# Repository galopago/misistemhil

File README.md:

# MISISTEMHIL

## INTERFACE FOR AUTOMATED TESTS (HARDWARE-IN-THE-LOOP). SOLDERLESS, MODULAR AND OPEN SOURCE

Electronic hardware prototyping system. Solderless, robust and open source. Solves the typical problem of the circuit that works on a breadboard but stops working on a real-world setup. Easy to replicate and compatible with virtually every electronic module.

Misistemhil is an open source project by [Galopago](https://galopago.github.io/)

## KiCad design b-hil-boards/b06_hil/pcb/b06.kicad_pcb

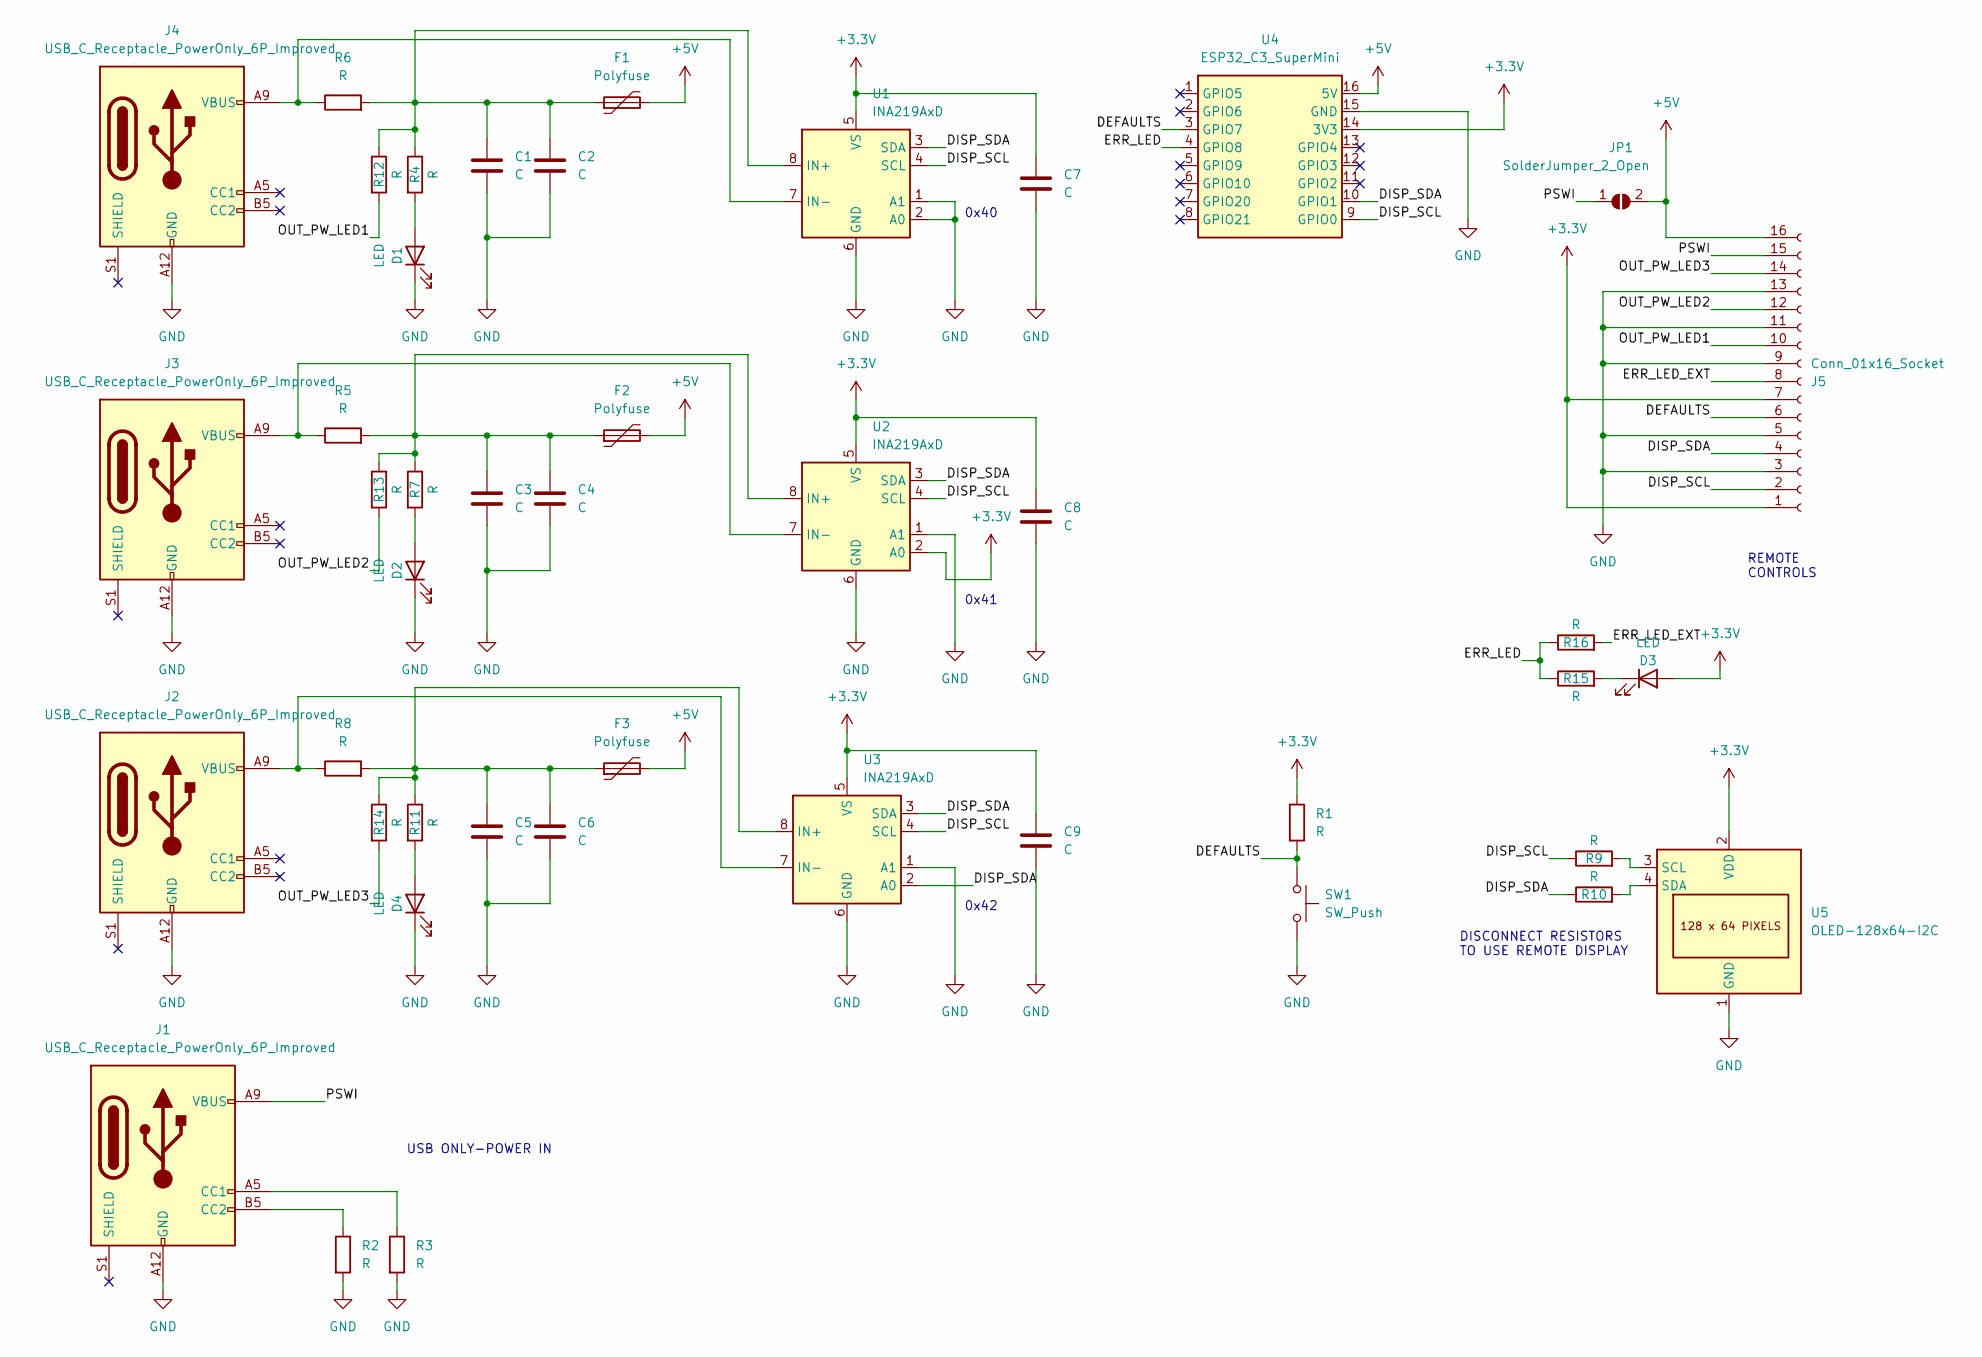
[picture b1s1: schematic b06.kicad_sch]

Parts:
C1, C3, C5: C; CP_Elec_8x10.5
C2, C4, C6, C7, C8, C9: C; C_0805_2012Metric_Pad1.18x1.45mm_HandSolder
D1, D2, D3, D4: LED; LED_0805_2012Metric_Pad1.15x1.40mm_HandSolder
F1, F2, F3: Polyfuse; Fuse_1206_3216Metric_Pad1.42x1.75mm_HandSolder
J1, J2, J3, J4: USB_C_Receptacle_PowerOnly_6P_Improved; USB_C_Receptacle_HRO_TYPE-C-31-M-12
J5: Conn_01x16_Socket; TerminalBlock_DoubleLevel_2x08_P3.50mm_Horizontal
JP1: SolderJumper_2_Open; SolderJumper-2_P1.3mm_Open_RoundedPad1.0x1.5mm
R1, R2, R3, R4, R7, R9, R10, R11, R12, R13, R14, R15, R16: R; R_0805_2012Metric_Pad1.20x1.40mm_HandSolder
R5, R6, R8: R; R_2512_6332Metric_Pad1.40x3.35mm_HandSolder
SW1: SW_Push; SW_Push_1P1T_NO_6x6mm_H9.5mm
U1, U2, U3: INA219AxD; SOIC-8_3.9x4.9mm_P1.27mm
U4: ESP32_C3_SuperMini; ESP32 C3 SuperMini
U5: OLED-128x64-I2C

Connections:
+3.3V: C7.1, C8.1, C9.1, D3.2 (A), J5.1, J5.7, R1.1, U1.5 (VS), U2.2 (A0), U2.5 (VS), U3.5 (VS), U4.14 (3V3), U5.2 (VDD)
+5V: F1.2, F2.2, F3.2, J5.16, JP1.2 (B), U4.16 (5V)
/DEFAULTS: J5.6, R1.2, SW1.1, U4.3 (GPIO7)
/DISP_SCL: J5.2, R9.1, U1.4 (SCL), U2.4 (SCL), U3.4 (SCL), U4.9 (GPIO0)
/DISP_SDA: J5.4, R10.1, U1.3 (SDA), U2.3 (SDA), U3.2 (A0), U3.3 (SDA), U4.10 (GPIO1)
/ERR_LED: R15.1, R16.1, U4.4 (GPIO8)
/ERR_LED_EXT: J5.8, R16.2
/OUT_PW_LED1: J5.10, R12.2
/OUT_PW_LED2: J5.12, R13.2
/OUT_PW_LED3: J5.14, R14.2
/PSWI: J1.A4 (VBUS), J1.A9 (VBUS), J1.B4 (VBUS), J1.B9 (VBUS), J5.15, JP1.1 (A)
GND: C1.2, C2.2, C3.2, C4.2, C5.2, C6.2, C7.2, C8.2, C9.2, D1.1 (K), D2.1 (K), D4.1 (K), J1.A1 (GND), J1.A12 (GND), J1.B1 (GND), J1.B12 (GND), J2.A1 (GND), J2.A12 (GND), J2.B1 (GND), J2.B12 (GND), J3.A1 (GND), J3.A12 (GND), J3.B1 (GND), J3.B12 (GND), J4.A1 (GND), J4.A12 (GND), J4.B1 (GND), J4.B12 (GND), J5.3, J5.5, J5.9, J5.11, J5.13, R2.2, R3.2, SW1.2, U1.1 (A1), U1.2 (A0), U1.6 (GND), U2.1 (A1), U2.6 (GND), U3.1 (A1), U3.6 (GND), U4.15 (GND), U5.1 (GND)
unnamed: D1.2 (A), R4.2
unnamed: D2.2 (A), R7.2
unnamed: D3.1 (K), R15.2
unnamed: D4.2 (A), R11.2
unnamed: J1.A5 (CC1), R3.1
unnamed: J1.B5 (CC2), R2.1
unnamed: C1.1, C2.1, F1.1, R4.1, R6.2, R12.1, U1.8 (IN+)
unnamed: J4.A4 (VBUS), J4.A9 (VBUS), J4.B4 (VBUS), J4.B9 (VBUS), R6.1, U1.7 (IN-)
unnamed: C3.1, C4.1, F2.1, R5.2, R7.1, R13.1, U2.8 (IN+)
unnamed: J3.A4 (VBUS), J3.A9 (VBUS), J3.B4 (VBUS), J3.B9 (VBUS), R5.1, U2.7 (IN-)
unnamed: C5.1, C6.1, F3.1, R8.2, R11.1, R14.1, U3.8 (IN+)
unnamed: J2.A4 (VBUS), J2.A9 (VBUS), J2.B4 (VBUS), J2.B9 (VBUS), R8.1, U3.7 (IN-)
unnamed: R9.2, U5.3 (SCL)
unnamed: R10.2, U5.4 (SDA)

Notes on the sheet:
0x41
0x42
REMOTE CONTROLS
0x40
DISCONNECT RESISTORS TO USE REMOTE DISPLAY
USB ONLY-POWER IN

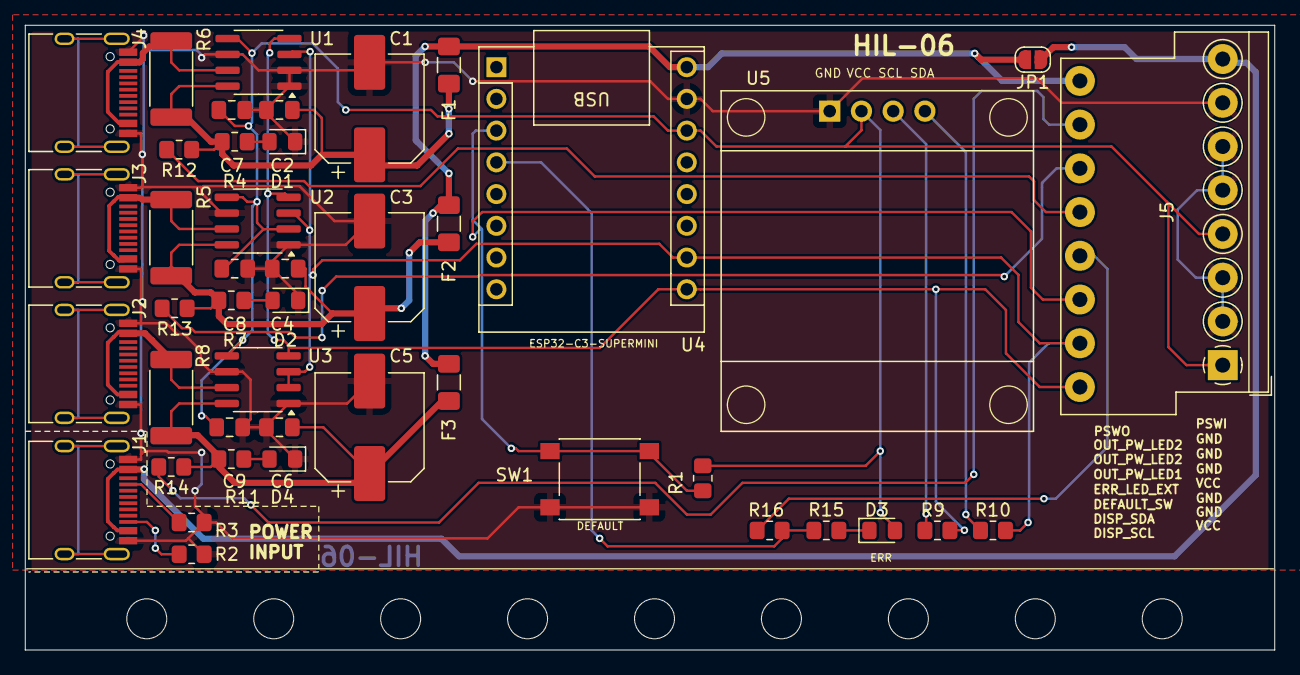
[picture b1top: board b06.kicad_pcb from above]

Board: 2 copper layers, 100.0 x 50.0 mm, 53 parts (0 on the bottom side), 26 nets.

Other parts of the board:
MH01, MH02, MH03, MH04, MH05, MH06, MH07, MH08, MH09: MountingHole_3.2mm_M3

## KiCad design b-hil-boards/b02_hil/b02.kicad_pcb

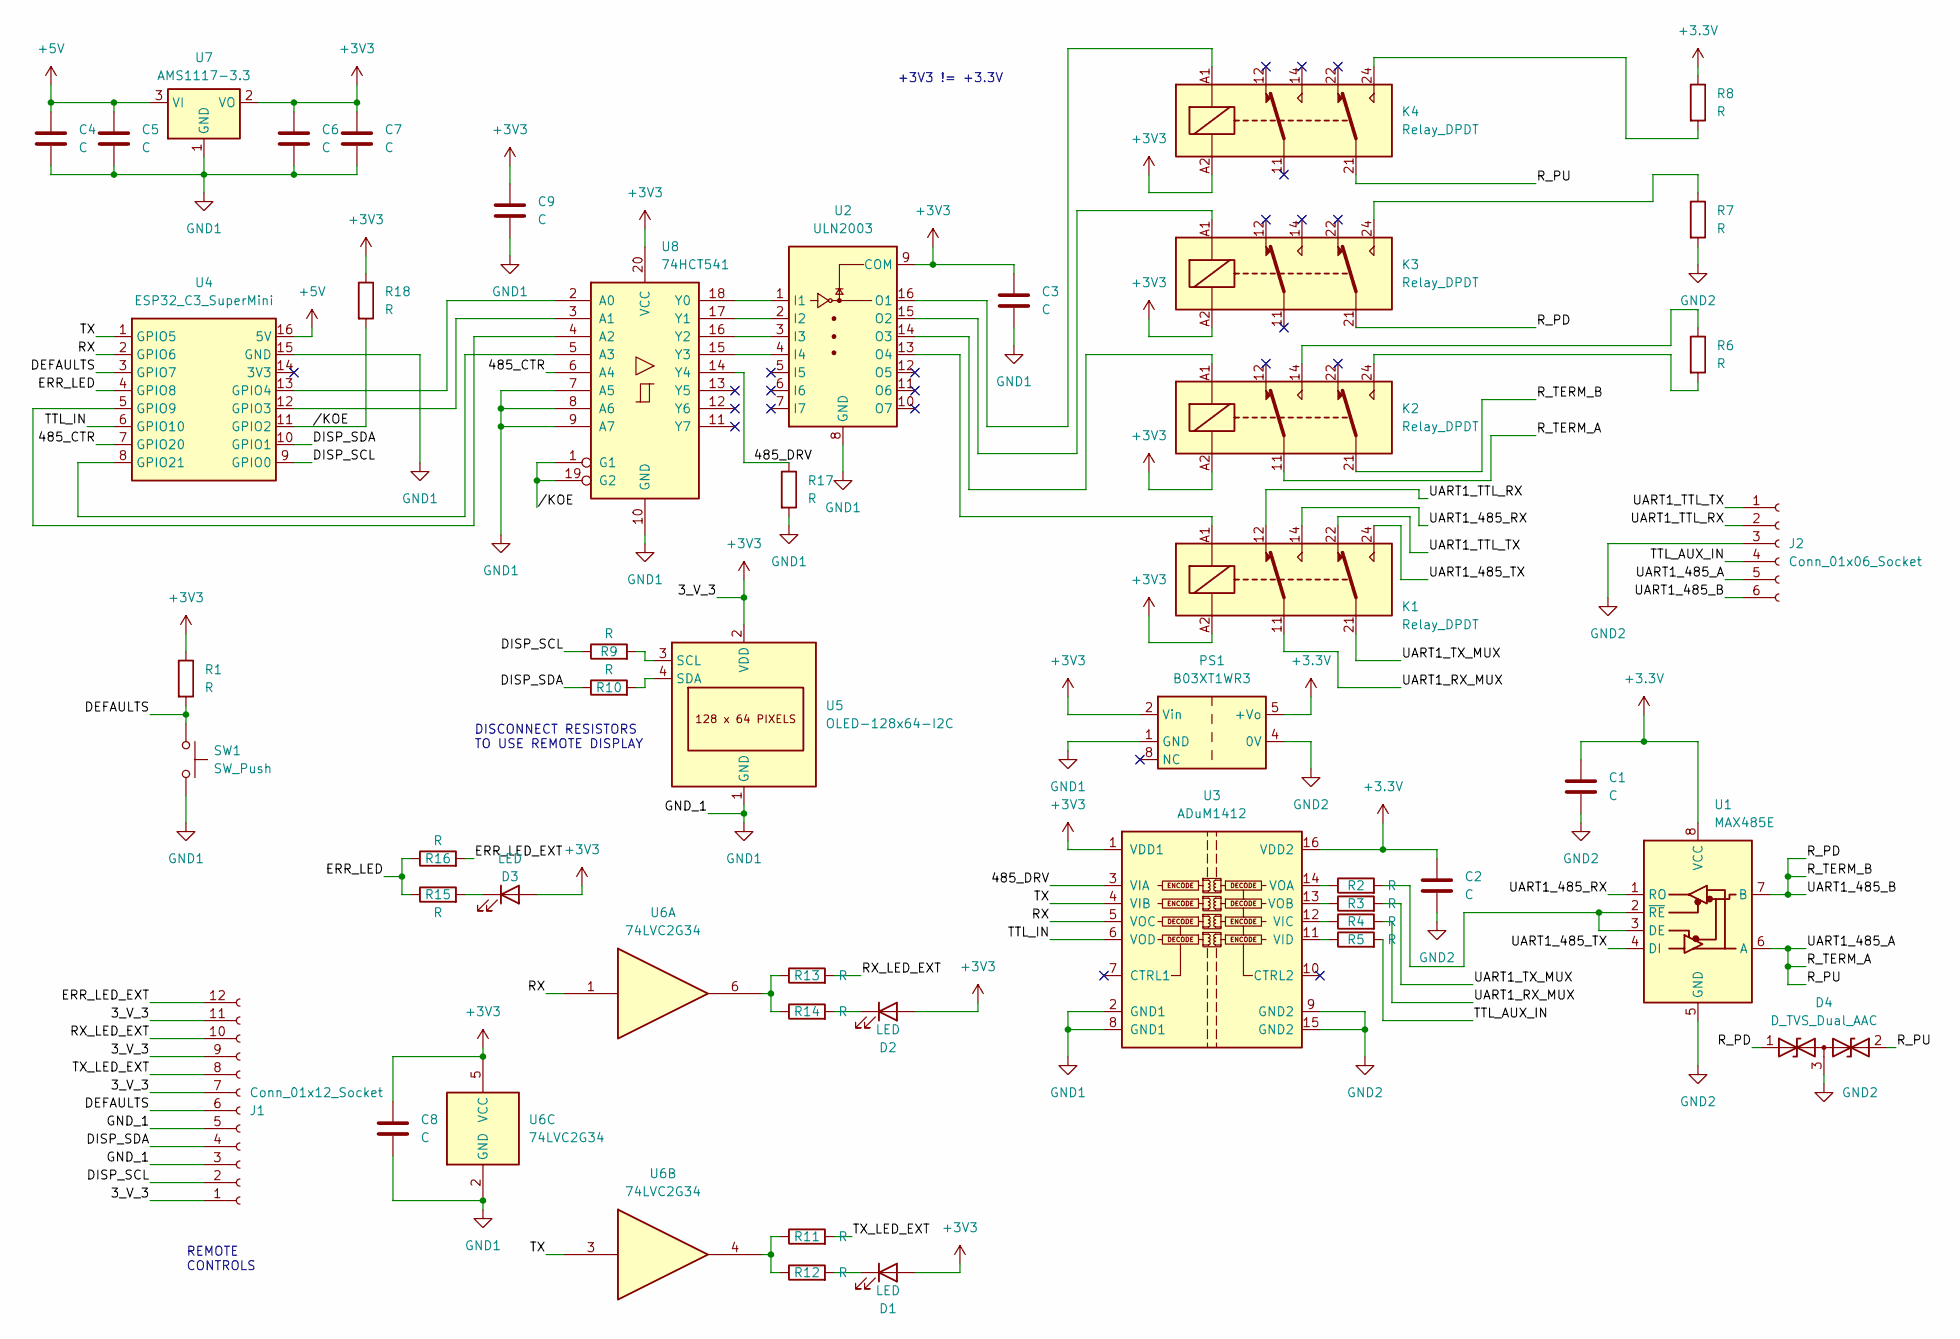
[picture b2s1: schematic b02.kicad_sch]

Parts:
C1, C2, C3, C4, C5, C6, C7, C8, C9: C; C_0805_2012Metric_Pad1.18x1.45mm_HandSolder
D1, D2, D3: LED; LED_0805_2012Metric_Pad1.15x1.40mm_HandSolder
D4: D_TVS_Dual_AAC; SOT-23-3
J1: Conn_01x12_Socket; TerminalBlock_DoubleLevel_2x06_P3.50mm_Horizontal
J2: Conn_01x06_Socket; TerminalBlock_DoubleLevel_2x03_P3.50mm_Horizontal
K1, K2, K3, K4: Relay_DPDT; Relay_DPDT_Omron_G6K-2F-Y
PS1: B03XT1WR3; Converter_DCDC_Mornsun_B03_XT_1WR3_SMD
R1, R2, R3, R4, R5, R6, R7, R8, R9, R10, R11, R12, R13, R14, R15, R16, R17, R18: R; R_0805_2012Metric_Pad1.20x1.40mm_HandSolder
SW1: SW_Push; SW_Push_1P1T_NO_6x6mm_H9.5mm
U1: MAX485E; SOIC-8_3.9x4.9mm_P1.27mm
U2: ULN2003; SOIC-16_3.9x9.9mm_P1.27mm
U3: ADuM1412; SOIC-16W_7.5x10.3mm_P1.27mm
U4: ESP32_C3_SuperMini; ESP32 C3 SuperMini
U5: OLED-128x64-I2C
U6: 74LVC2G34; SOT-23-6_Handsoldering
U7: AMS1117-3.3; SOT-223-3_TabPin2
U8: 74HCT541; TSSOP-20_4.4x6.5mm_P0.65mm

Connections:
+3.3V: C1.1, C2.1, PS1.5 (+Vo), R8.1, U1.8 (VCC), U3.16 (VDD2)
+3V3: C3.1, C6.1, C7.1, C8.1, C9.1, D1.2 (A), D2.2 (A), D3.2 (A), J1.1, J1.7, J1.9, J1.11, K1.A2, K2.A2, K3.A2, K4.A2, PS1.2 (Vin), R1.1, R18.1, U2.9 (COM), U3.1 (VDD1), U5.2 (VDD), U6.5 (VCC), U7.2 (VO), U8.20 (VCC)
+5V: C4.1, C5.1, U4.16 (5V), U7.3 (VI)
/485_CTR: U4.7 (GPIO20), U8.6 (A4)
/485_DRV: R17.1, U3.3 (VIA), U8.14 (Y4)
/DEFAULTS: J1.6, R1.2, SW1.1, U4.3 (GPIO7)
/DISP_SCL: J1.2, R9.1, U4.9 (GPIO0)
/DISP_SDA: J1.4, R10.1, U4.10 (GPIO1)
/ERR_LED: R15.1, R16.1, U4.4 (GPIO8)
/ERR_LED_EXT: J1.12, R16.2
/RX: U3.5 (VOC), U4.2 (GPIO6), U6.1
/RX_LED_EXT: J1.10, R13.2
/R_PD: D4.1 (A1), J2.6, K2.21, K3.21, U1.7 (B)
/R_PU: D4.2 (A2), J2.5, K2.11, K4.21, U1.6 (A)
/TTL_AUX_IN: J2.4, R5.2
/TTL_IN: U3.6 (VOD), U4.6 (GPIO10)
/TX: U3.4 (VIB), U4.1 (GPIO5), U6.3
/TX_LED_EXT: J1.8, R11.2
/UART1_485_RX: K1.14, U1.1 (RO)
/UART1_485_TX: K1.24, U1.4 (DI)
/UART1_RX_MUX: K1.11, R4.2
/UART1_TTL_RX: J2.2, K1.12
/UART1_TTL_TX: J2.1, K1.22
/UART1_TX_MUX: K1.21, R3.2
//KOE: R18.2, U4.11 (GPIO2), U8.1 (G1), U8.19 (G2)
GND1: C3.2, C4.2, C5.2, C6.2, C7.2, C8.2, C9.2, J1.3, J1.5, PS1.1 (GND), R17.2, SW1.2, U2.8 (GND), U3.2 (GND1), U3.8 (GND1), U4.15 (GND), U5.1 (GND), U6.2 (GND), U7.1 (GND), U8.7 (A5), U8.8 (A6), U8.9 (A7), U8.10 (GND)
GND2: C1.2, C2.2, D4.3 (common), J2.3, PS1.4 (0V), R7.2, U1.5 (GND), U3.9 (GND2), U3.15 (GND2)
unnamed: D1.1 (K), R12.2
unnamed: D2.1 (K), R14.2
unnamed: D3.1 (K), R15.2
unnamed: K2.14, R6.1
unnamed: K2.24, R6.2
unnamed: K3.24, R7.1
unnamed: K4.24, R8.2
unnamed: R11.1, R12.1, U6.4
unnamed: R13.1, R14.1, U6.6
unnamed: R2.2, U1.2 (~RE), U1.3 (DE)
unnamed: U2.1 (I1), U8.18 (Y0)
unnamed: U2.2 (I2), U8.17 (Y1)
unnamed: U2.3 (I3), U8.16 (Y2)
unnamed: U2.4 (I4), U8.15 (Y3)
unnamed: K4.A1, U2.16 (O1)
unnamed: K3.A1, U2.15 (O2)
unnamed: K2.A1, U2.14 (O3)
unnamed: K1.A1, U2.13 (O4)
unnamed: R4.1, U3.12 (VIC)
unnamed: R5.1, U3.11 (VID)
unnamed: R2.1, U3.14 (VOA)
unnamed: R3.1, U3.13 (VOB)
unnamed: U4.12 (GPIO3), U8.3 (A1)
unnamed: U4.13 (GPIO4), U8.2 (A0)
unnamed: U4.5 (GPIO9), U8.4 (A2)
unnamed: U4.8 (GPIO21), U8.5 (A3)
unnamed: R9.2, U5.3 (SCL)
unnamed: R10.2, U5.4 (SDA)

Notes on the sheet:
+3V3 != +3.3V
REMOTE CONTROLS
DISCONNECT RESISTORS TO USE REMOTE DISPLAY

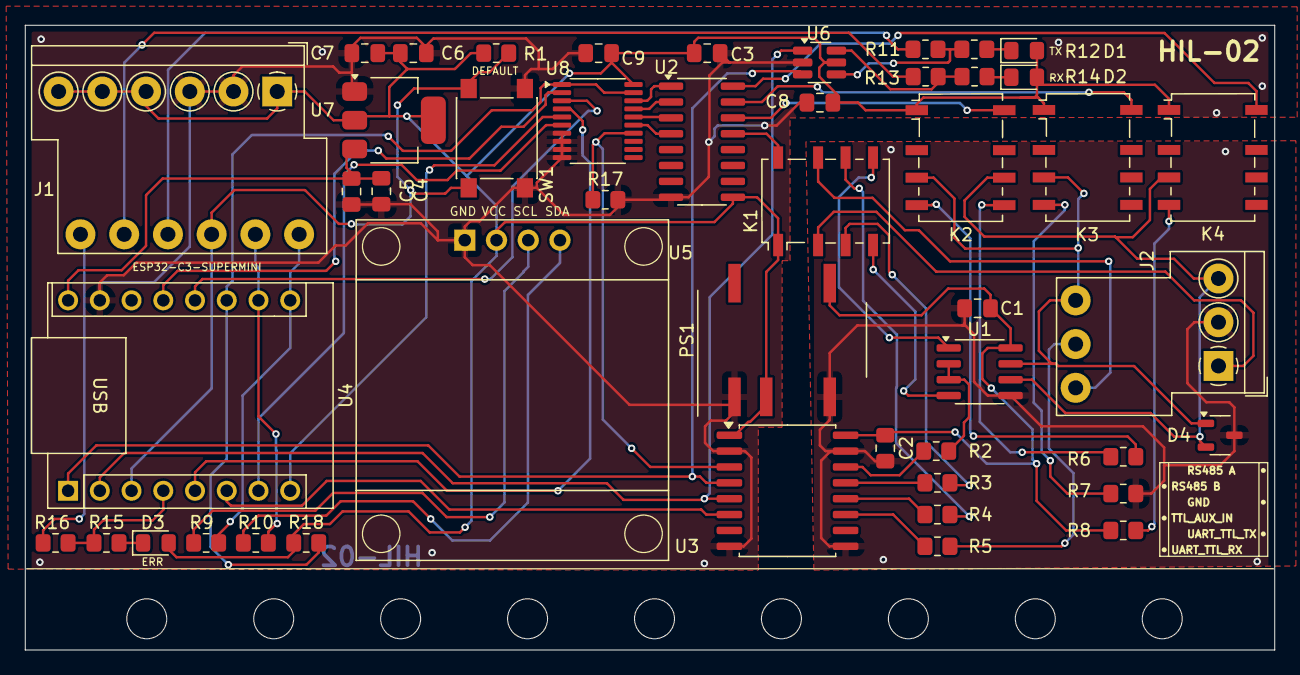
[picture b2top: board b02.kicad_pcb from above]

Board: 2 copper layers, 100.0 x 50.0 mm, 56 parts (0 on the bottom side), 55 nets.

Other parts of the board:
MH01, MH02, MH03, MH04, MH05, MH06, MH07, MH08, MH09: MountingHole_3.2mm_M3

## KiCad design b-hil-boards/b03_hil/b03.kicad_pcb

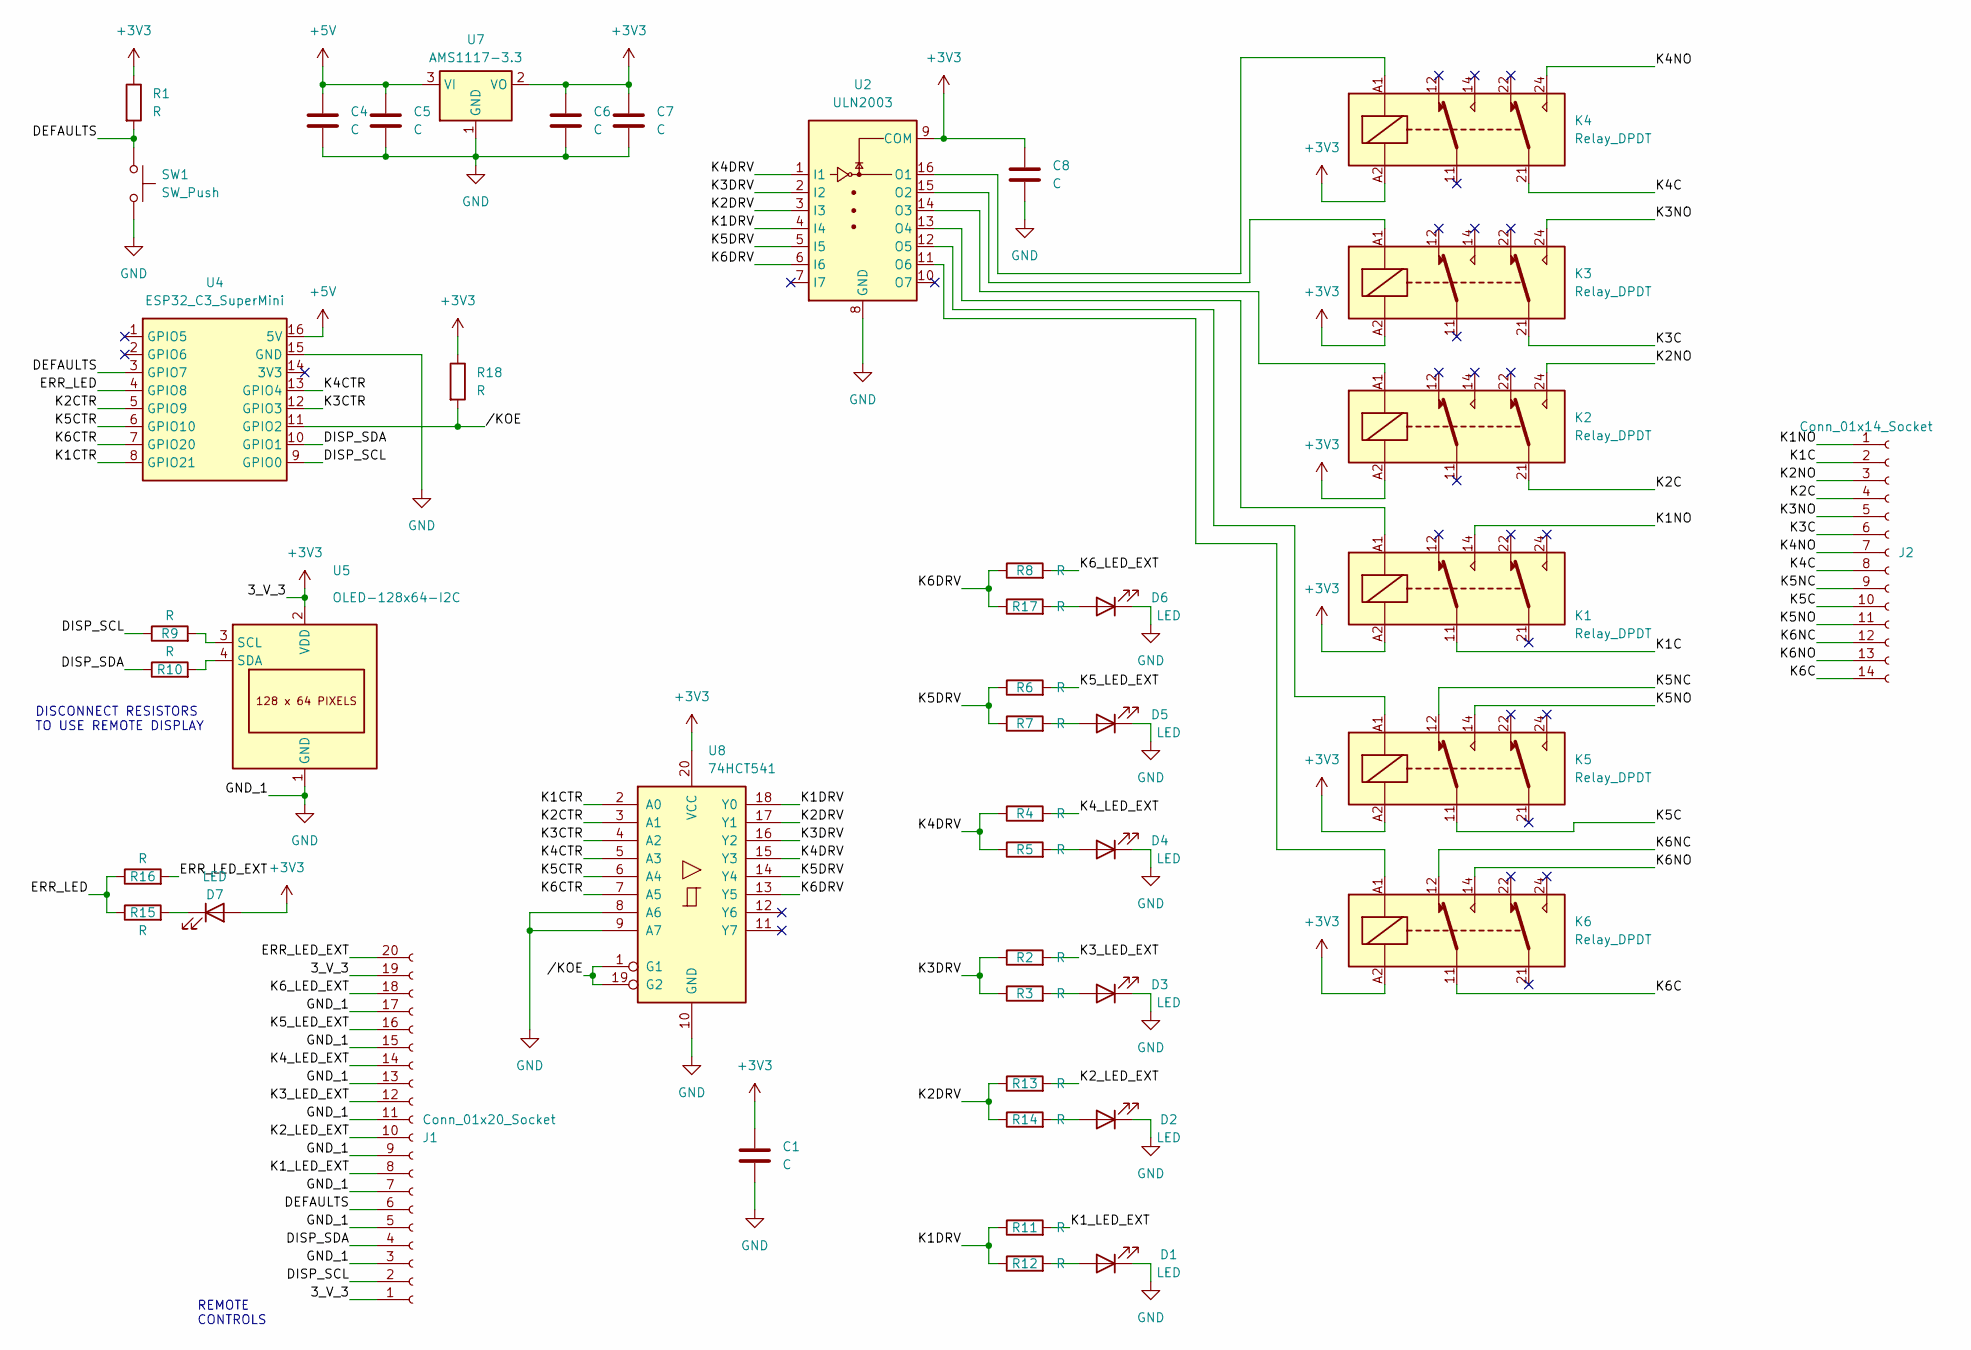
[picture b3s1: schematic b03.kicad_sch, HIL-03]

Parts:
C1, C4, C5, C6, C7, C8: C; C_0805_2012Metric_Pad1.18x1.45mm_HandSolder
D1, D2, D3, D4, D5, D6, D7: LED; LED_0805_2012Metric_Pad1.15x1.40mm_HandSolder
J1: Conn_01x20_Socket; TerminalBlock_DoubleLevel_2x10_P3.50mm_Horizontal
J2: Conn_01x14_Socket; TerminalBlock_DoubleLevel_2x07_P3.50mm_Horizontal
K1, K2, K3, K4, K5, K6: Relay_DPDT; Relay_DPDT_Omron_G6K-2F-Y
R1, R2, R3, R4, R5, R6, R7, R8, R9, R10, R11, R12, R13, R14, R15, R16, R17, R18: R; R_0805_2012Metric_Pad1.20x1.40mm_HandSolder
SW1: SW_Push; SW_Push_1P1T_NO_6x6mm_H9.5mm
U2: ULN2003; SOIC-16_3.9x9.9mm_P1.27mm
U4: ESP32_C3_SuperMini; ESP32 C3 SuperMini
U5: OLED-128x64-I2C
U7: AMS1117-3.3; SOT-223-3_TabPin2
U8: 74HCT541; TSSOP-20_4.4x6.5mm_P0.65mm

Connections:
+3V3: C1.1, C6.1, C7.1, C8.1, D7.2 (A), J1.1, J1.19, K1.A2, K2.A2, K3.A2, K4.A2, K5.A2, K6.A2, R1.1, R18.1, U2.9 (COM), U5.2 (VDD), U7.2 (VO), U8.20 (VCC)
+5V: C4.1, C5.1, U4.16 (5V), U7.3 (VI)
/DEFAULTS: J1.6, R1.2, SW1.1, U4.3 (GPIO7)
/DISP_SCL: J1.2, R9.1, U4.9 (GPIO0)
/DISP_SDA: J1.4, R10.1, U4.10 (GPIO1)
/ERR_LED: R15.1, R16.1, U4.4 (GPIO8)
/ERR_LED_EXT: J1.20, R16.2
/K1C: J2.2, K1.11
/K1CTR: U4.8 (GPIO21), U8.2 (A0)
/K1DRV: R11.1, R12.1, U2.4 (I4), U8.18 (Y0)
/K1NO: J2.1, K1.14
/K1_LED_EXT: J1.8, R11.2
/K2C: J2.4, K2.21
/K2CTR: U4.5 (GPIO9), U8.3 (A1)
/K2DRV: R13.1, R14.1, U2.3 (I3), U8.17 (Y1)
/K2NO: J2.3, K2.24
/K2_LED_EXT: J1.10, R13.2
/K3C: J2.6, K3.21
/K3CTR: U4.12 (GPIO3), U8.4 (A2)
/K3DRV: R2.1, R3.1, U2.2 (I2), U8.16 (Y2)
/K3NO: J2.5, K3.24
/K3_LED_EXT: J1.12, R2.2
/K4C: J2.8, K4.21
/K4CTR: U4.13 (GPIO4), U8.5 (A3)
/K4DRV: R4.1, R5.1, U2.1 (I1), U8.15 (Y3)
/K4NO: J2.7, K4.24
/K4_LED_EXT: J1.14, R4.2
/K5C: J2.10, K5.11
/K5CTR: U4.6 (GPIO10), U8.6 (A4)
/K5DRV: R6.1, R7.1, U2.5 (I5), U8.14 (Y4)
/K5NC: J2.9, K5.12
/K5NO: J2.11, K5.14
/K5_LED_EXT: J1.16, R6.2
/K6C: J2.14, K6.11
/K6CTR: U4.7 (GPIO20), U8.7 (A5)
/K6DRV: R8.1, R17.1, U2.6 (I6), U8.13 (Y5)
/K6NC: J2.12, K6.12
/K6NO: J2.13, K6.14
/K6_LED_EXT: J1.18, R8.2
//KOE: R18.2, U4.11 (GPIO2), U8.1 (G1), U8.19 (G2)
GND: C1.2, C4.2, C5.2, C6.2, C7.2, C8.2, D1.1 (K), D2.1 (K), D3.1 (K), D4.1 (K), D5.1 (K), D6.1 (K), J1.3, J1.5, J1.7, J1.9, J1.11, J1.13, J1.15, J1.17, SW1.2, U2.8 (GND), U4.15 (GND), U5.1 (GND), U7.1 (GND), U8.8 (A6), U8.9 (A7), U8.10 (GND)
unnamed: D1.2 (A), R12.2
unnamed: D2.2 (A), R14.2
unnamed: D3.2 (A), R3.2
unnamed: D4.2 (A), R5.2
unnamed: D5.2 (A), R7.2
unnamed: D6.2 (A), R17.2
unnamed: D7.1 (K), R15.2
unnamed: K4.A1, U2.16 (O1)
unnamed: K3.A1, U2.15 (O2)
unnamed: K2.A1, U2.14 (O3)
unnamed: K1.A1, U2.13 (O4)
unnamed: K5.A1, U2.12 (O5)
unnamed: K6.A1, U2.11 (O6)
unnamed: R9.2, U5.3 (SCL)
unnamed: R10.2, U5.4 (SDA)

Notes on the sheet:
REMOTE CONTROLS
DISCONNECT RESISTORS TO USE REMOTE DISPLAY

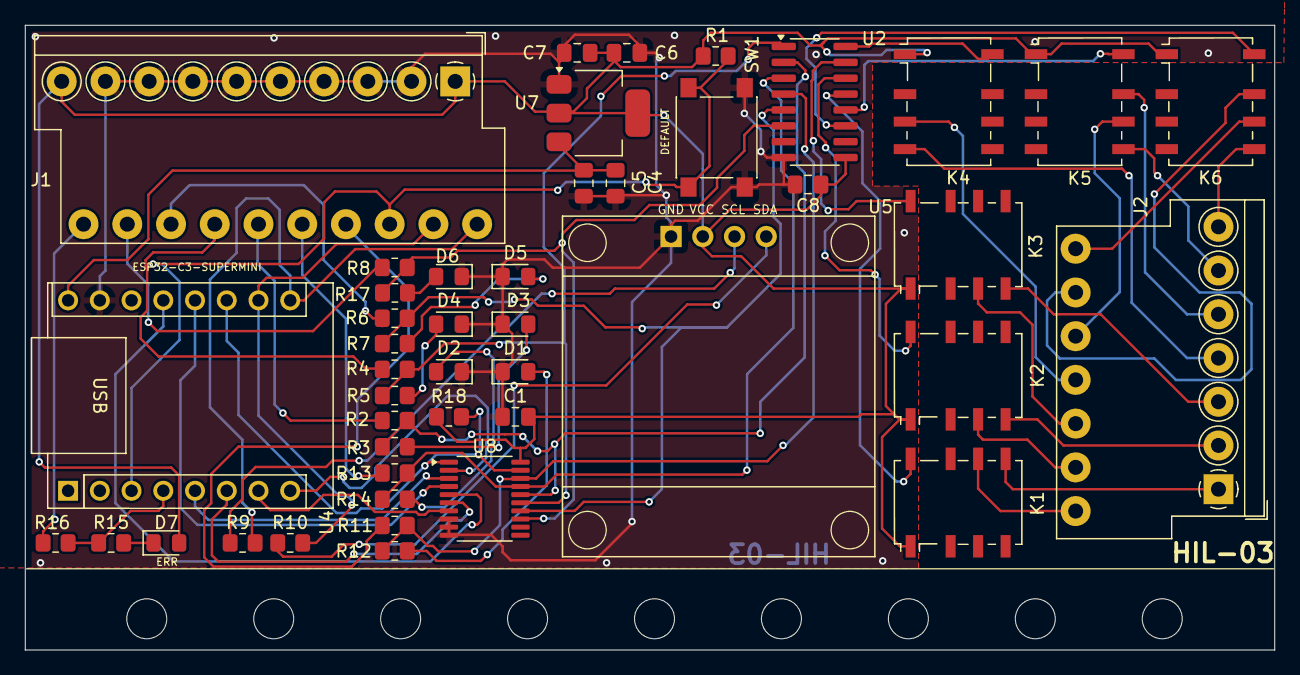
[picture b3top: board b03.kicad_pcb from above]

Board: 2 copper layers, 100.0 x 50.0 mm, 54 parts (0 on the bottom side), 56 nets.

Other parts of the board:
MH01, MH02, MH03, MH04, MH05, MH06, MH07, MH08, MH09: MountingHole_3.2mm_M3

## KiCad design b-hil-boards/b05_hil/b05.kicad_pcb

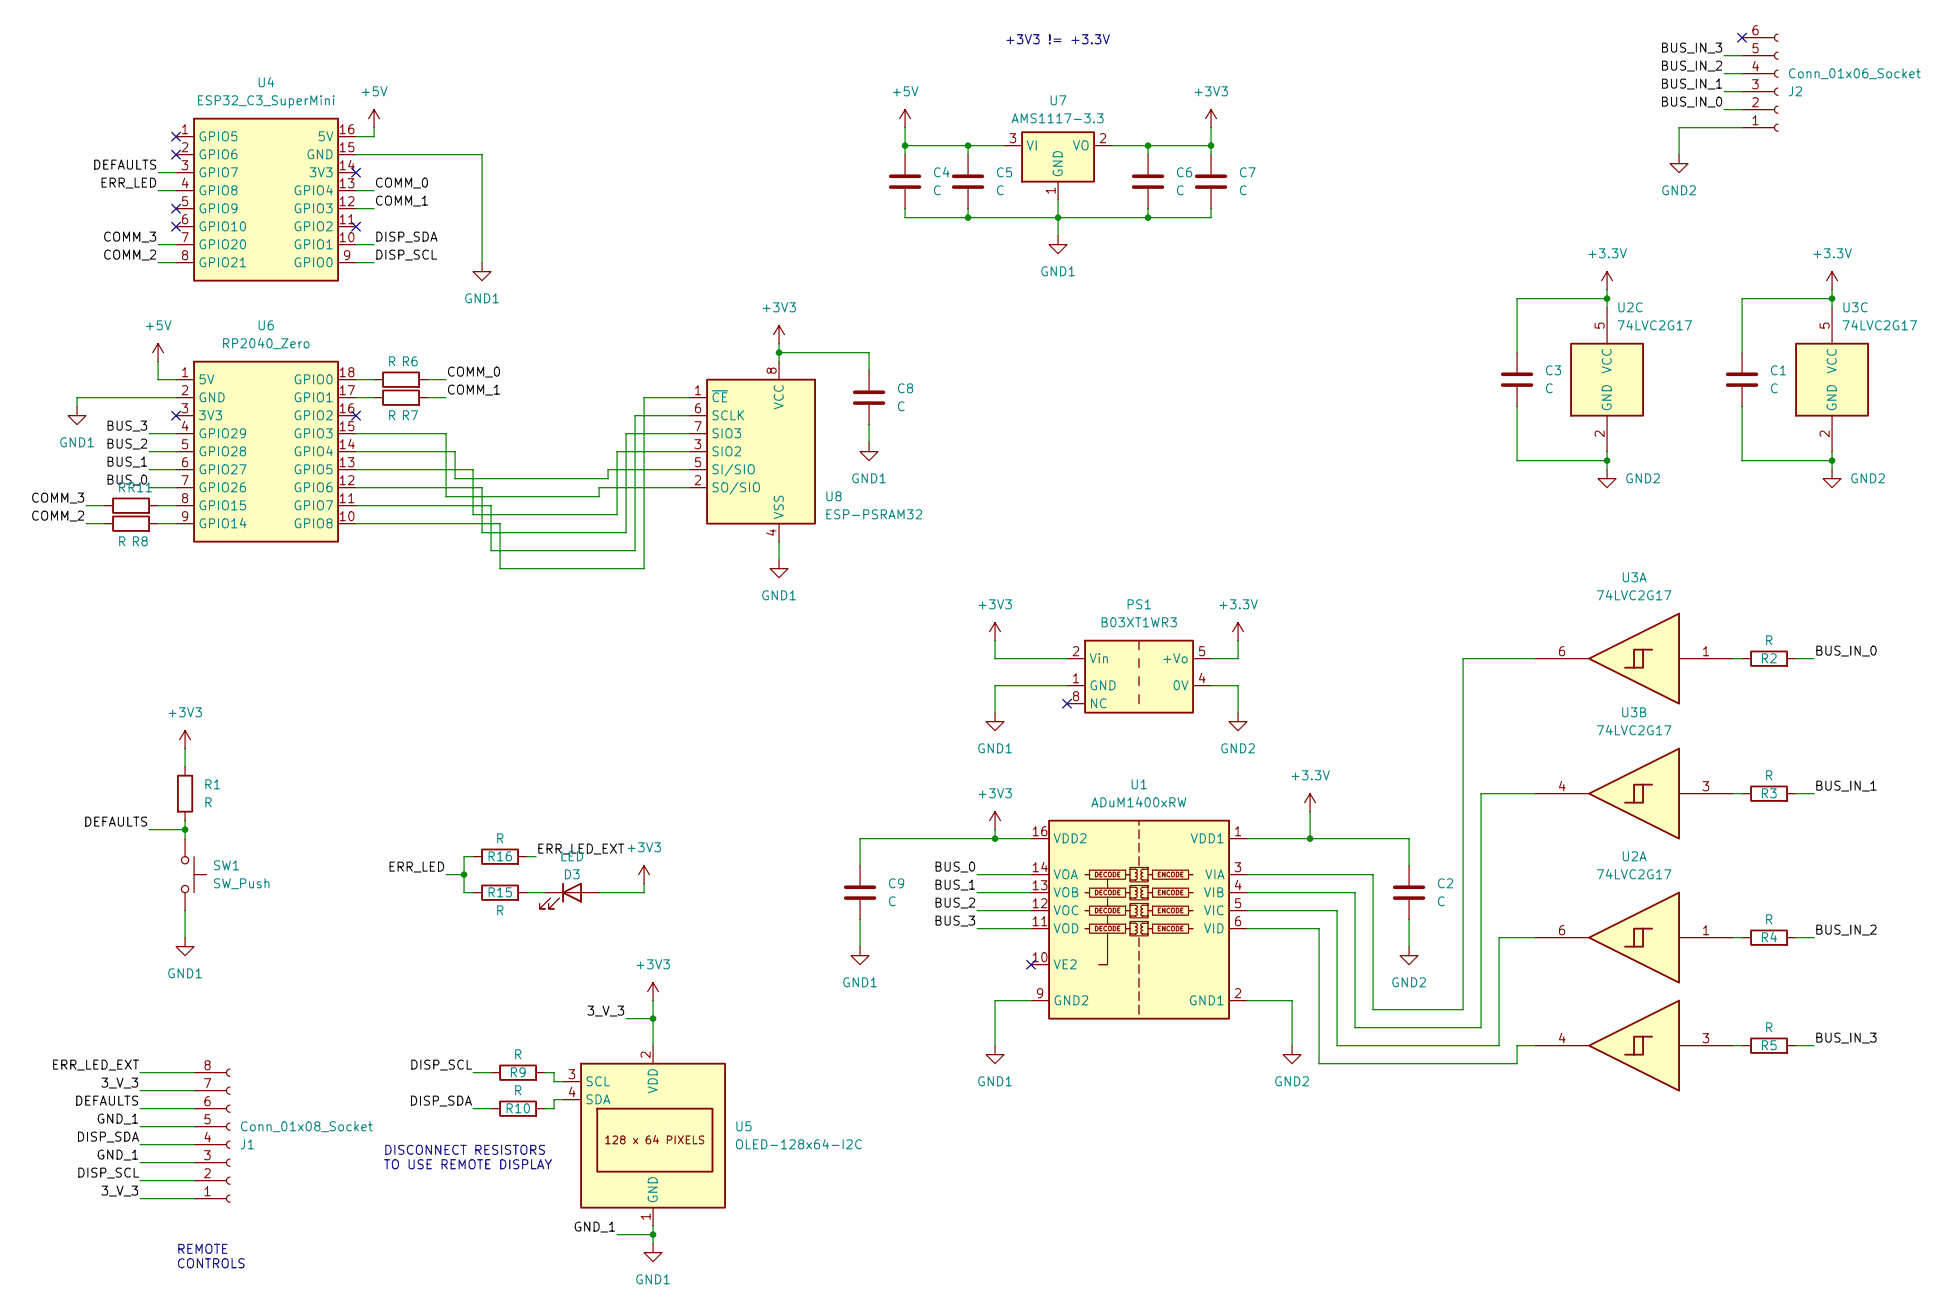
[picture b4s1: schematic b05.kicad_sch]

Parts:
C1, C2, C3, C4, C5, C6, C7, C8, C9: C; C_0805_2012Metric_Pad1.18x1.45mm_HandSolder
D3: LED; LED_0805_2012Metric_Pad1.15x1.40mm_HandSolder
J1: Conn_01x08_Socket; TerminalBlock_DoubleLevel_2x04_P3.50mm_Horizontal
J2: Conn_01x06_Socket; TerminalBlock_DoubleLevel_2x03_P3.50mm_Horizontal
PS1: B03XT1WR3; Converter_DCDC_Mornsun_B03_XT_1WR3_SMD
R1, R2, R3, R4, R5, R6, R7, R8, R9, R10, R11, R15, R16: R; R_0805_2012Metric_Pad1.20x1.40mm_HandSolder
SW1: SW_Push; SW_Push_1P1T_NO_6x6mm_H9.5mm
U1: ADuM1400xRW; SOIC-16W_7.5x10.3mm_P1.27mm
U2, U3: 74LVC2G17; SOT-23-6_Handsoldering
U4: ESP32_C3_SuperMini; ESP32 C3 SuperMini
U5: OLED-128x64-I2C
U6: RP2040_Zero; RP2040 Zero
U7: AMS1117-3.3; SOT-223-3_TabPin2
U8: ESP-PSRAM32; SOIC-8_3.9x4.9mm_P1.27mm

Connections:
+3.3V: C1.1, C2.1, C3.1, PS1.5 (+Vo), U1.1 (VDD1), U2.5 (VCC), U3.5 (VCC)
+3V3: C6.1, C7.1, C8.1, C9.1, D3.2 (A), J1.1, J1.7, PS1.2 (Vin), R1.1, U1.16 (VDD2), U5.2 (VDD), U7.2 (VO), U8.8 (VCC)
+5V: C4.1, C5.1, U4.16 (5V), U6.1 (5V), U7.3 (VI)
/BUS_0: U1.14 (VOA), U6.7 (GPIO26)
/BUS_1: U1.13 (VOB), U6.6 (GPIO27)
/BUS_2: U1.12 (VOC), U6.5 (GPIO28)
/BUS_3: U1.11 (VOD), U6.4 (GPIO29)
/BUS_IN_0: J2.2, R2.2
/BUS_IN_1: J2.3, R3.2
/BUS_IN_2: J2.4, R4.2
/BUS_IN_3: J2.5, R5.2
/COMM_0: R6.2, U4.13 (GPIO4)
/COMM_1: R7.2, U4.12 (GPIO3)
/COMM_2: R8.1, U4.8 (GPIO21)
/COMM_3: R11.1, U4.7 (GPIO20)
/DEFAULTS: J1.6, R1.2, SW1.1, U4.3 (GPIO7)
/DISP_SCL: J1.2, R9.1, U4.9 (GPIO0)
/DISP_SDA: J1.4, R10.1, U4.10 (GPIO1)
/ERR_LED: R15.1, R16.1, U4.4 (GPIO8)
/ERR_LED_EXT: J1.8, R16.2
GND1: C4.2, C5.2, C6.2, C7.2, C8.2, C9.2, J1.3, J1.5, PS1.1 (GND), SW1.2, U1.9 (GND2), U1.15 (GND2), U4.15 (GND), U5.1 (GND), U6.2 (GND), U7.1 (GND), U8.4 (VSS)
GND2: C1.2, C2.2, C3.2, J2.1, PS1.4 (0V), U1.2 (GND1), U1.8 (GND1), U2.2 (GND), U3.2 (GND)
unnamed: D3.1 (K), R15.2
unnamed: R2.1, U3.1
unnamed: R3.1, U3.3
unnamed: R4.1, U2.1
unnamed: R5.1, U2.3
unnamed: U1.3 (VIA), U3.6
unnamed: U1.4 (VIB), U3.4
unnamed: U1.5 (VIC), U2.6
unnamed: U1.6 (VID), U2.4
unnamed: R9.2, U5.3 (SCL)
unnamed: R10.2, U5.4 (SDA)
unnamed: R6.1, U6.18 (GPIO0)
unnamed: R7.1, U6.17 (GPIO1)
unnamed: U6.15 (GPIO3), U8.2 (SO/SIO)
unnamed: U6.14 (GPIO4), U8.5 (SI/SIO)
unnamed: U6.13 (GPIO5), U8.3 (SIO2)
unnamed: U6.12 (GPIO6), U8.7 (SIO3)
unnamed: U6.11 (GPIO7), U8.6 (SCLK)
unnamed: U6.10 (GPIO8), U8.1 (~CE)
unnamed: R8.2, U6.9 (GPIO14)
unnamed: R11.2, U6.8 (GPIO15)

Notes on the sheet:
+3V3 != +3.3V
REMOTE CONTROLS
DISCONNECT RESISTORS TO USE REMOTE DISPLAY

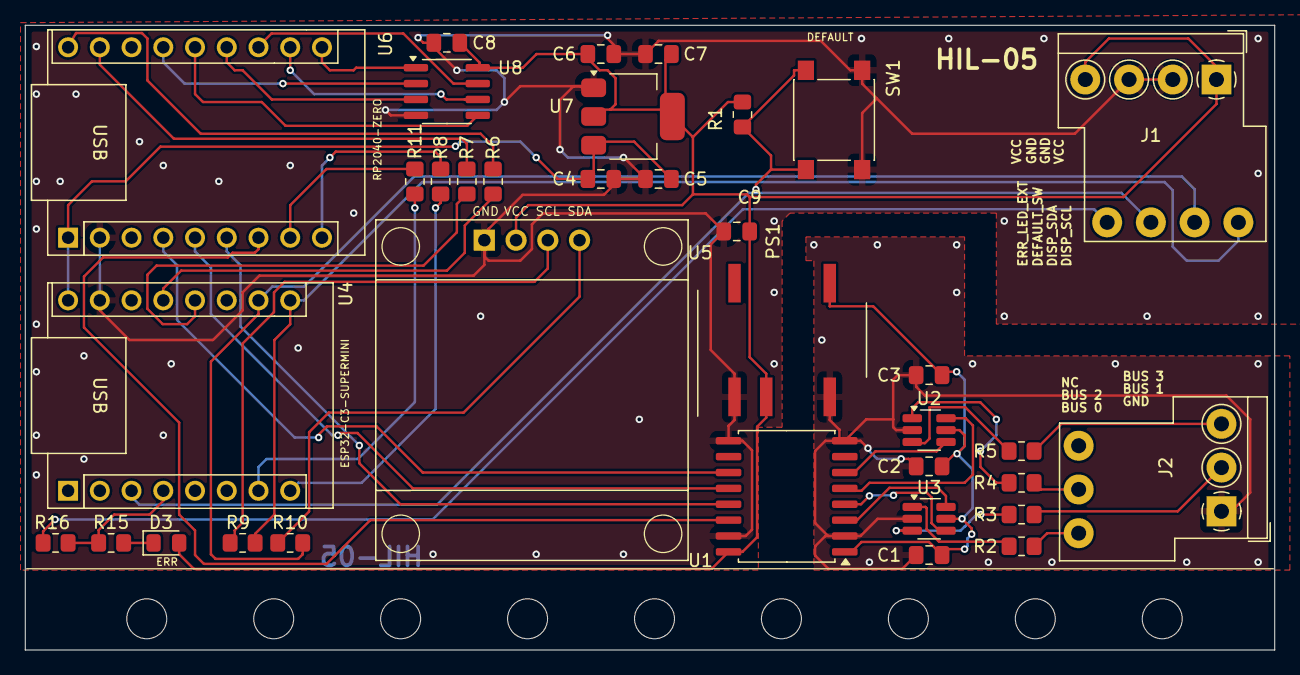
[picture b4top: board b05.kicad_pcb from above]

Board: 2 copper layers, 100.0 x 50.0 mm, 44 parts (0 on the bottom side), 43 nets.

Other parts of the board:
MH01, MH02, MH03, MH04, MH05, MH06, MH07, MH08, MH09: MountingHole_3.2mm_M3
